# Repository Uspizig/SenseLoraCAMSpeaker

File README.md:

# SenseLoRaCAMSpeaker: The Programmable Addon Board for Xiao Sense S3 for LoRa and Audio

## Features:

1. **AudioAmplifier MAX98357**: Listen to your favourite Tunes with an Audio Amplifier

2. **I2C Connector for Sensor**: Connect your favourite I2C Sensor board with the embedded 2.54mm connector

3. **LoRa**: Long Range Communication like Meshtastikm, The Thingsnetwork or Helium

4. **Wireless Control**: Untehther your development process with the wireless capabilities. With WiFi, Lora and BLE, this tool allows remote control and data logging. Users can adjust settings and monitor data from a distance, offering a more flexible development experience.

5. **Open Source & Programmable**: As an open-source device, the Device offers unmatched versatility. It is fully programmable, allowing you to tailor its functionality to your specific applications. This customization extends to software and hardware, opening up endless possibilities for creative and efficient project development.

6. **Compact Design**: Designed for convenience, the LoRaCam Board compact and sleek form factor allows for seamless integration into existing setups. Its compatibility with USB PD power sources and inline integration capability minimizes the need for additional equipment or extensive redesign, making it a versatile and user-friendly addition to any development environment.

7. **Display**: Monitor live the current status

8. **LoRa**: Operate the Device in remote areas without Wifi in Standalone mode

9. **RGB LED**: Status LED
## Specifications

### Key Features:

### Future Developments:

AI Detection of objects and determine if the device shall sent the data via LoRa 

## Testing for Performance

At the heart of SenseLoRaCam's design is a commitment to reliability and performance. To ensure that SenseLoRaCam stands up to real-world demands, we subjected it to testing under use conditions.

## License

MIT License

Copyright (c) 2025 blue2monster

Permission is hereby granted, free of charge, to any person obtaining a copy
of this software and associated documentation files (the "Software"), to deal
in the Software without restriction, including without limitation the rights
to use, copy, modify, merge, publish, distribute, sublicense, and/or sell
copies of the Software, and to permit persons to whom the Software is
furnished to do so, subject to the following conditions:

The above copyright notice and this permission notice shall be included in all
copies or substantial portions of the Software.

THE SOFTWARE IS PROVIDED "AS IS", WITHOUT WARRANTY OF ANY KIND, EXPRESS OR
IMPLIED, INCLUDING BUT NOT LIMITED TO THE WARRANTIES OF MERCHANTABILITY,
FITNESS FOR A PARTICULAR PURPOSE AND NONINFRINGEMENT. IN NO EVENT SHALL THE
AUTHORS OR COPYRIGHT HOLDERS BE LIABLE FOR ANY CLAIM, DAMAGES OR OTHER
LIABILITY, WHETHER IN AN ACTION OF CONTRACT, TORT OR OTHERWISE, ARISING FROM,
OUT OF OR IN CONNECTION WITH THE SOFTWARE OR THE USE OR OTHER DEALINGS IN THE
SOFTWARE.

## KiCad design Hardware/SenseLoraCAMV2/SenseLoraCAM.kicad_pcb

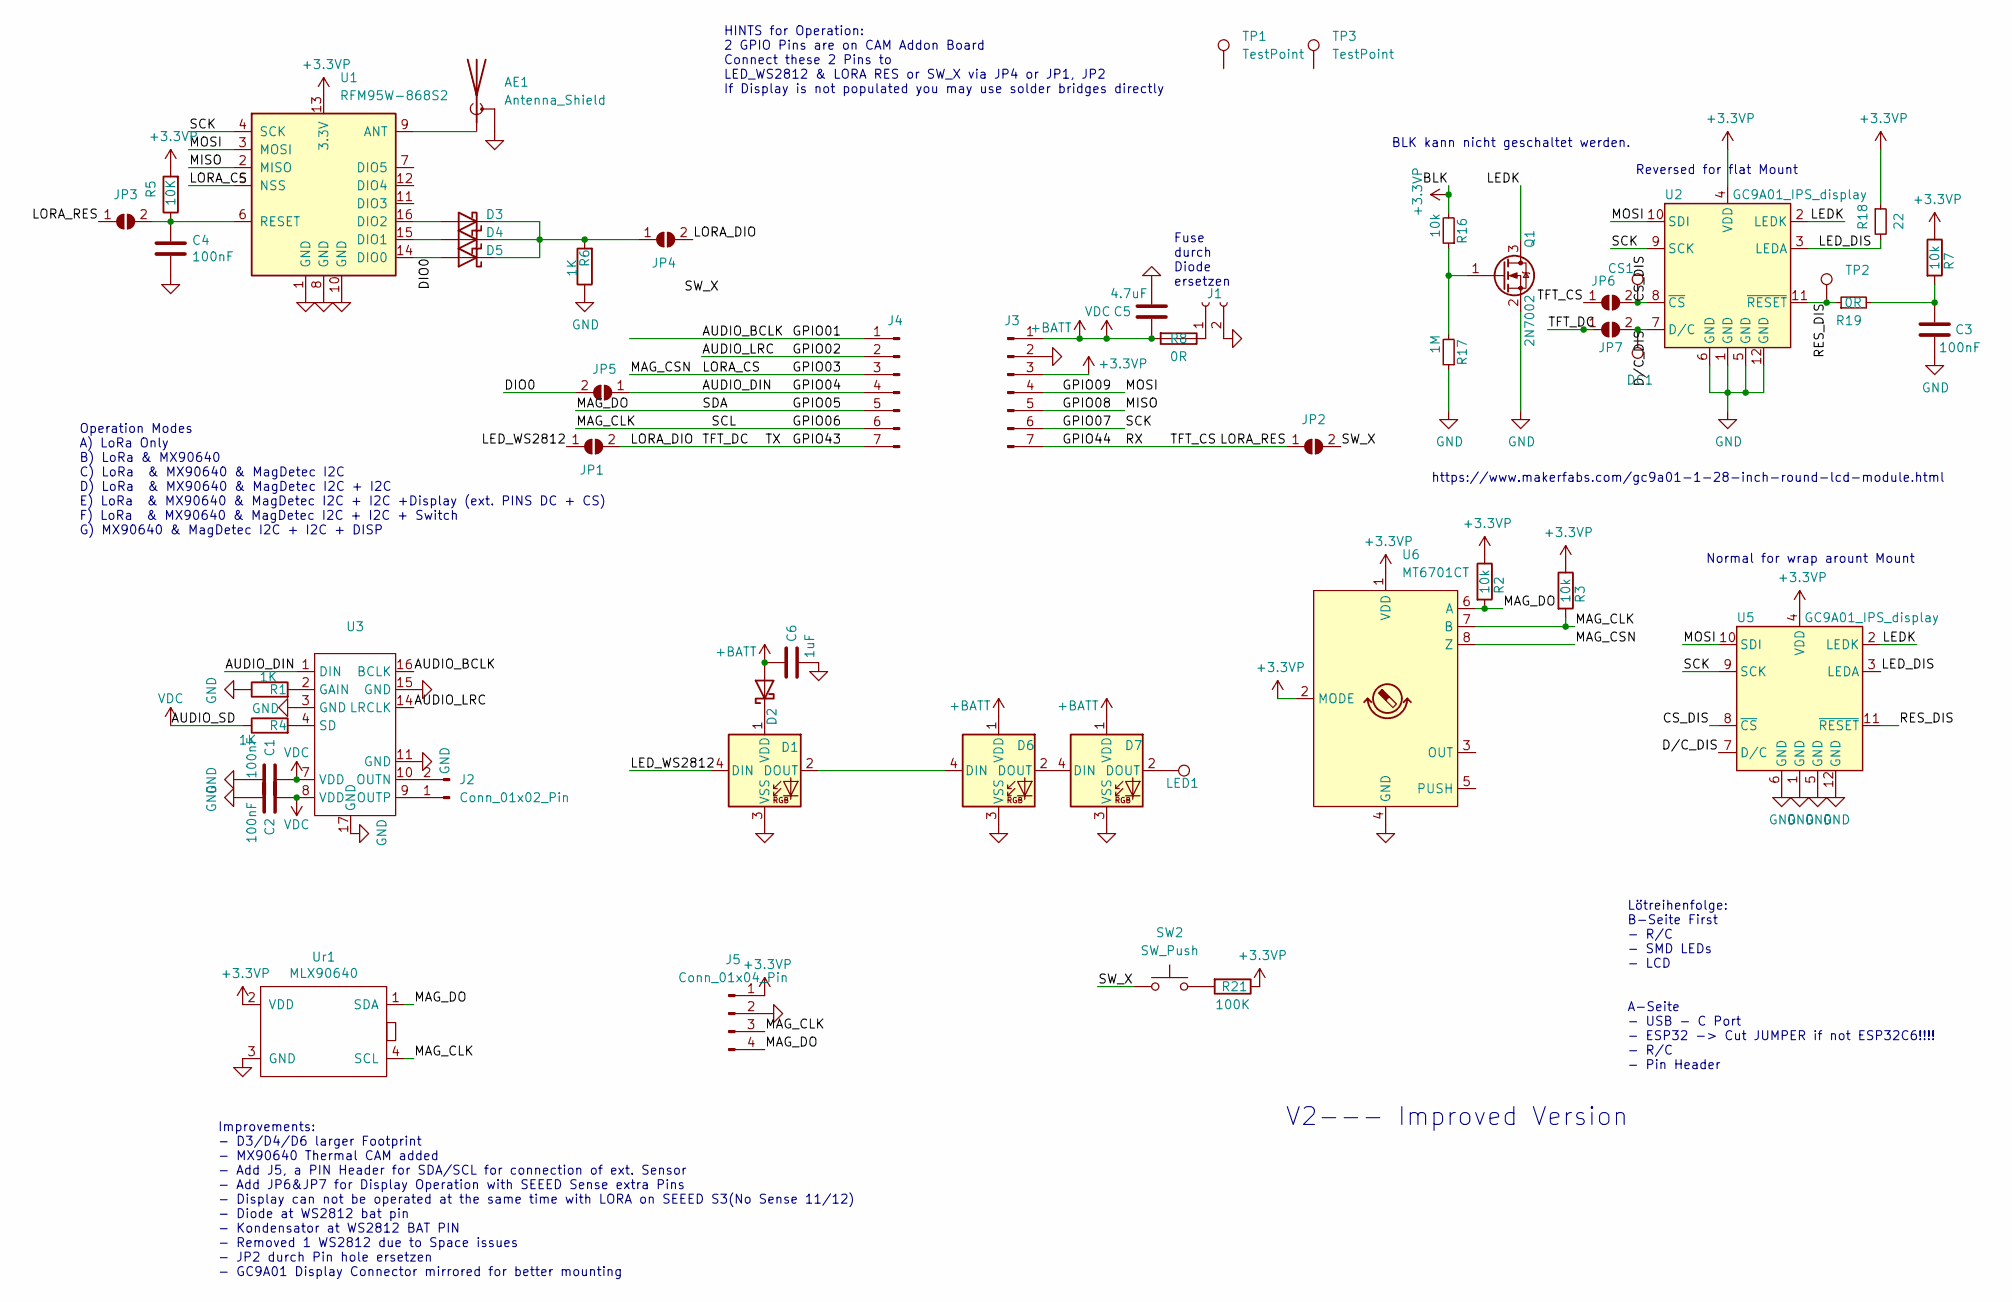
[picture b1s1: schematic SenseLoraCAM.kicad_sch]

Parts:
AE1: Antenna_Shield; SMA_Samtec_SMA-J-P-X-ST-EM1_EdgeMount
C1, C2, C3, C4: 100nF; C_0805_2012Metric_Pad1.18x1.45mm_HandSolder
C5: 4.7uF; C_0805_2012Metric_Pad1.18x1.45mm_HandSolder
C6: 1uF; C_0805_2012Metric_Pad1.18x1.45mm_HandSolder
CS1: TestPoint; TestPoint_Pad_D1.5mm
D1, D6, D7: WS2812B; LED_WS2812B_PLCC4_5.0x5.0mm_P3.2mm
D2, D3, D4, D5: MBR0530; D_SOD-123
DC1: TestPoint; TestPoint_Pad_D1.5mm
J1: Conn_01x02_Female; JST_GH_SM02B-GHS-TB_1x02-1MP_P1.25mm_Horizontal
J2: Conn_01x02_Pin; PinHeader_1x02_P2.54mm_Vertical
J3, J4: Conn_01x07_Pin; PinHeader_1x07_P2.54mm_Vertical
J5: Conn_01x04_Pin; PinHeader_1x04_P2.54mm_Vertical_SMD_Pin1Right
JP1, JP2, JP3, JP5, JP6, JP7: SolderJumper_2_Open; SolderJumper-2_P1.3mm_Open_RoundedPad1.0x1.5mm
JP4: SolderJumper_2_Open; SolderJumper-2_P1.3mm_Bridged_RoundedPad1.0x1.5mm
LED1: TestPoint; TestPoint_Pad_1.5x1.5mm
Q1: 2N7002; SOT-23
R1, R4, R6: 1K; R_0805_2012Metric_Pad1.20x1.40mm_HandSolder
R2, R3, R7: 10k; R_0805_2012Metric_Pad1.20x1.40mm_HandSolder
R5: 10K; R_0805_2012Metric_Pad1.20x1.40mm_HandSolder
R8, R19: 0R; R_0805_2012Metric_Pad1.20x1.40mm_HandSolder
R16: 10k; R_0603_1608Metric
R17: 1M; R_0805_2012Metric_Pad1.20x1.40mm_HandSolder
R18: 22; R_0603_1608Metric
R21: 100K; R_0805_2012Metric_Pad1.20x1.40mm_HandSolder
SW2: SW_Push; SW_SPST_CK_KMS2xxGP
TP1, TP3: TestPoint; baerklein
TP2: TestPoint; TestPoint_Pad_D1.0mm
U1: RFM95W-868S2; HOPERF_RFM9XW_SMD
U2: GC9A01_IPS_display; GC9A01_IPS_display_reversed
U3: TQFN-16_L3.0-W3.0-P0.50-BL-EP1.5
U5: GC9A01_IPS_display
U6: MT6701CT; SO-8_3.9x4.9mm_P1.27mm
Ur1: MLX90640; Part Number 482-MLX90640ESFBABSP

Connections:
+3.3VP: J3.3, J5.1, R2.1, R3.1, R5.2, R7.1, R16.2, R18.1, R21.1, U1.13 (3.3V), U2.4 (VDD), U5.4 (VDD), U6.1 (VDD), U6.2 (MODE), Ur1.2 (VDD)
+BATT: C1.1, C2.1, C5.1, C6.1, D2.2 (A), D6.1 (VDD), D7.1 (VDD), J3.1, R4.1, R8.2, U3.7 (VDD), U3.8 (VDD)
/AUDIO_BCLK: J4.1, U3.16 (BCLK)
/AUDIO_DIN: J4.4, JP5.1 (A), U3.1 (DIN)
/AUDIO_LRC: J4.2, U3.14 (LRCLK)
/CS_DIS: CS1.1, JP6.2 (B), U2.8 (~CS), U5.8 (~CS); also elsewhere on the board
/DIO0: D5.2 (A), JP5.2 (B), U1.14 (DIO0)
/D/C_DIS: DC1.1, JP7.2 (B), U2.7 (D/C), U5.7 (D/C); also elsewhere on the board
/GPIO03: J4.3, U1.5 (NSS), U6.8 (Z)
/GPIO05: J4.5, J5.4, R2.2, U6.6 (A), Ur1.1 (SDA)
/GPIO06: J4.6, J5.3, R3.2, U6.7 (B), Ur1.4 (SCL)
/GPIO07: J3.6, U1.4 (SCK), U2.9 (SCK), U5.9 (SCK)
/GPIO08: J3.5, U1.2 (MISO)
/GPIO09: J3.4, U1.3 (MOSI), U2.10 (SDI), U5.10 (SDI)
/GPIO43: J4.7, JP1.2 (B), JP4.2 (B), JP7.1 (A)
/GPIO44: J3.7, JP2.1 (A), JP3.1 (A), JP6.1 (A)
/LEDK: Q1.3 (D), U2.2 (LEDK), U5.2 (LEDK)
/LED_DIS: R18.2, U2.3 (LEDA), U5.3 (LEDA)
/LED_WS2812: D1.4 (DIN), JP1.1 (A)
/RES_DIS: R19.1, TP2.1, U2.11 (~RESET), U5.11 (~RESET); also elsewhere on the board
/SW_X: JP2.2 (B), SW2.2
GND: AE1.2 (Shield), C1.2, C2.2, C3.2, C4.1, C5.2, C6.2, D1.3 (VSS), D6.3 (VSS), D7.3 (VSS), J1.2, J3.2, J5.2, Q1.2 (S), R1.1, R6.1, R17.1, U1.1 (GND), U1.8 (GND), U1.10 (GND), U2.1 (GND), U2.5 (GND), U2.6 (GND), U2.12 (GND), U3.3 (GND), U3.11 (GND), U3.15 (GND), U3.17 (GND), U5.1 (GND), U5.5 (GND), U5.6 (GND), U5.12 (GND), U6.4 (GND), Ur1.3 (GND)
unnamed: AE1.1 (A), U1.9 (ANT)
unnamed: C3.1, R7.2, R19.2
unnamed: D1.2 (DOUT), D6.4 (DIN)
unnamed: D1.1 (VDD), D2.1 (K)
unnamed: D3.2 (A), U1.16 (DIO2)
unnamed: D3.1 (K), D4.1 (K), D5.1 (K), JP4.1 (A), R6.2
unnamed: D4.2 (A), U1.15 (DIO1)
unnamed: D6.2 (DOUT), D7.4 (DIN)
unnamed 30: D7.2 (DOUT), LED1.1; also elsewhere on the board
unnamed: J1.1, R8.1
unnamed: J2.1, U3.9 (OUTP)
unnamed: J2.2, U3.10 (OUTN)
unnamed: C4.2, JP3.2 (B), R5.1, U1.6 (RESET)
unnamed: Q1.1 (G), R16.1, R17.2
unnamed: R21.2, SW2.1
unnamed: R1.2, U3.2 (GAIN)
unnamed: R4.2, U3.4 (SD)

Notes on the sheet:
Lötreihenfolge: B-Seite First - R/C - SMD LEDs - LCD A-Seite - USB - C Port - ESP32 -> Cut JUMPER if not ESP32C6!!!! - R/C - Pin Header
HINTS for Operation: 2 GPIO Pins are on CAM Addon Board Connect these 2 Pins to LED_WS2812 & LORA RES or SW_X via JP4 or JP1, JP2 If Display is not populated you may use solder bridges directly
Normal for wrap arount Mount
https://www.makerfabs.com/gc9a01-1-28-inch-round-lcd-module.html
V2--- Improved Version
Reversed for flat Mount
Fuse durch Diode ersetzen
Operation Modes A) LoRa Only B) LoRa & MX90640 C) LoRa & MX90640 & MagDetec I2C D) LoRa & MX90640 & MagDetec I2C + I2C E) LoRa & MX90640 & MagDetec I2C + I2C +Display (ext. PINS DC + CS) F) LoRa & MX90640 & MagDetec I2C + I2C + Switch G) MX90640 & MagDetec I2C + I2C + DISP
BLK kann nicht geschaltet werden.
Improvements: - D3/D4/D6 larger Footprint - MX90640 Thermal CAM added - Add J5, a PIN Header for SDA/SCL for connection of ext. Sensor - Add JP6&JP7 for Display Operation with SEEED Sense extra Pins - Display can not be operated at the same time with LORA on SEEED S3(No Sense 11/12) - Diode at WS28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

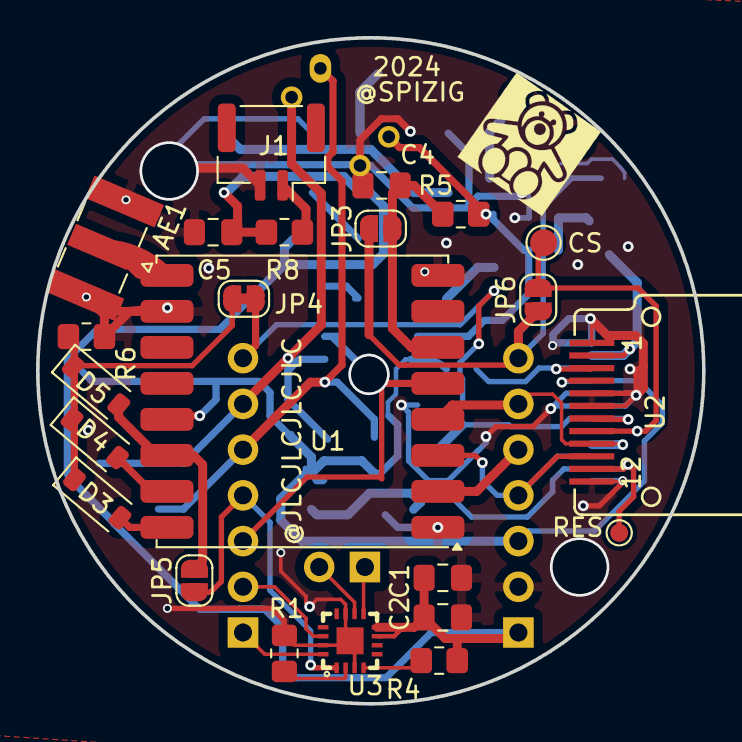
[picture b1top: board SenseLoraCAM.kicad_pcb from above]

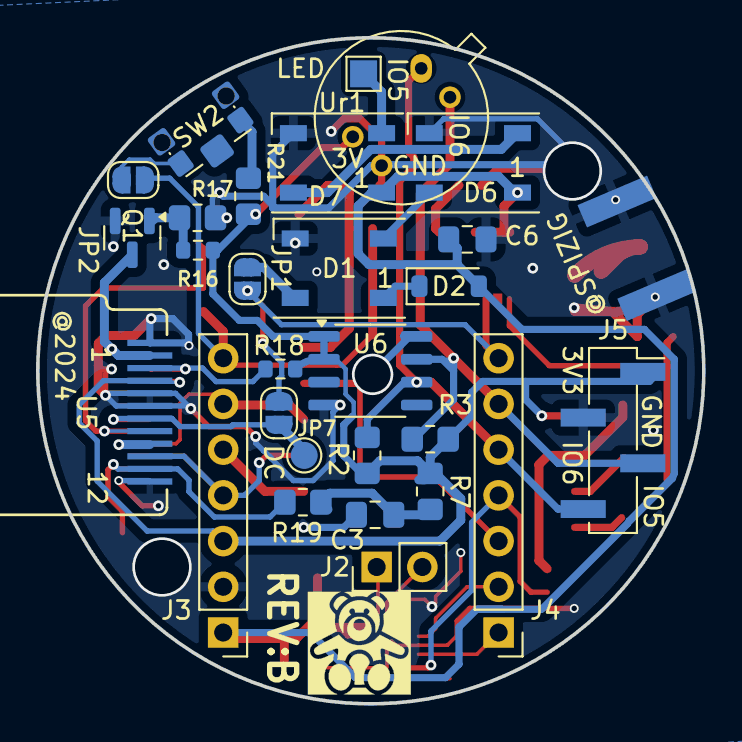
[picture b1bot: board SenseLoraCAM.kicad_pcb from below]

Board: 2 copper layers, 37.0 x 37.0 mm, 53 parts (29 on the bottom side), 39 nets.

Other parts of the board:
CS: TestPoint; TestPoint_Pad_D1.5mm
DC: TestPoint; TestPoint_Pad_D1.5mm
LED: TestPoint; TestPoint_Pad_1.5x1.5mm
RES: TestPoint; TestPoint_Pad_D1.0mm

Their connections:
/CS_DIS: CS.1; also elsewhere on the board
/D/C_DIS: DC.1; also elsewhere on the board
/RES_DIS: RES.1; also elsewhere on the board
unnamed 30: LED.1; also elsewhere on the board

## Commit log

2024-09-29 Add files via upload
    Initial Release
2024-09-29 Create LICENSE
